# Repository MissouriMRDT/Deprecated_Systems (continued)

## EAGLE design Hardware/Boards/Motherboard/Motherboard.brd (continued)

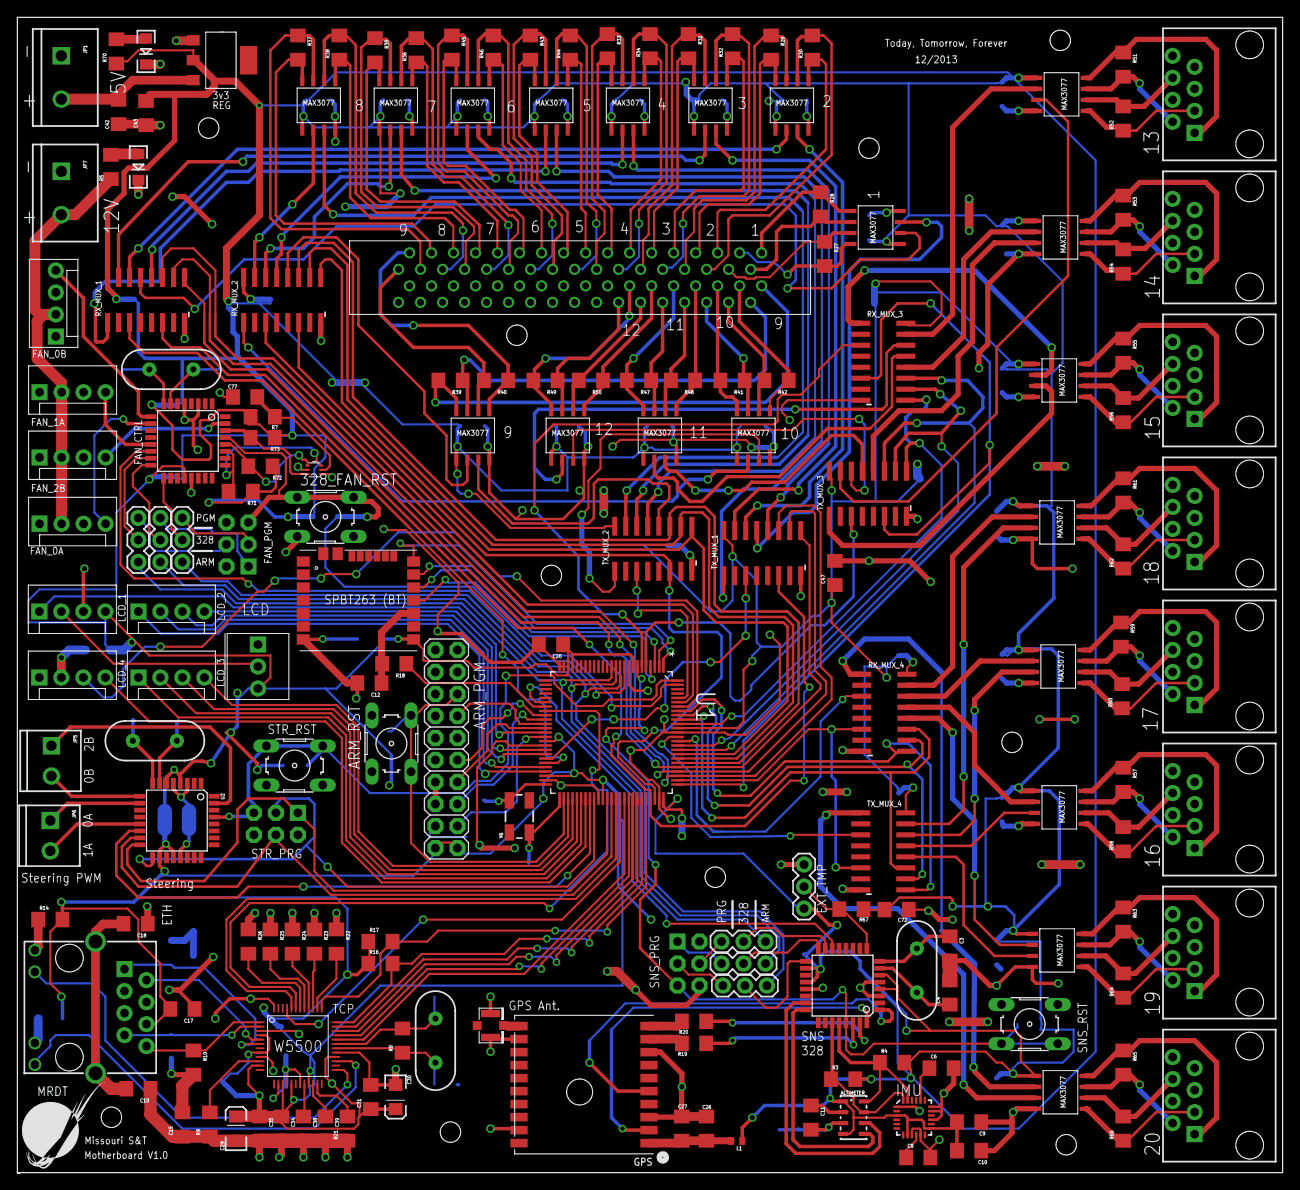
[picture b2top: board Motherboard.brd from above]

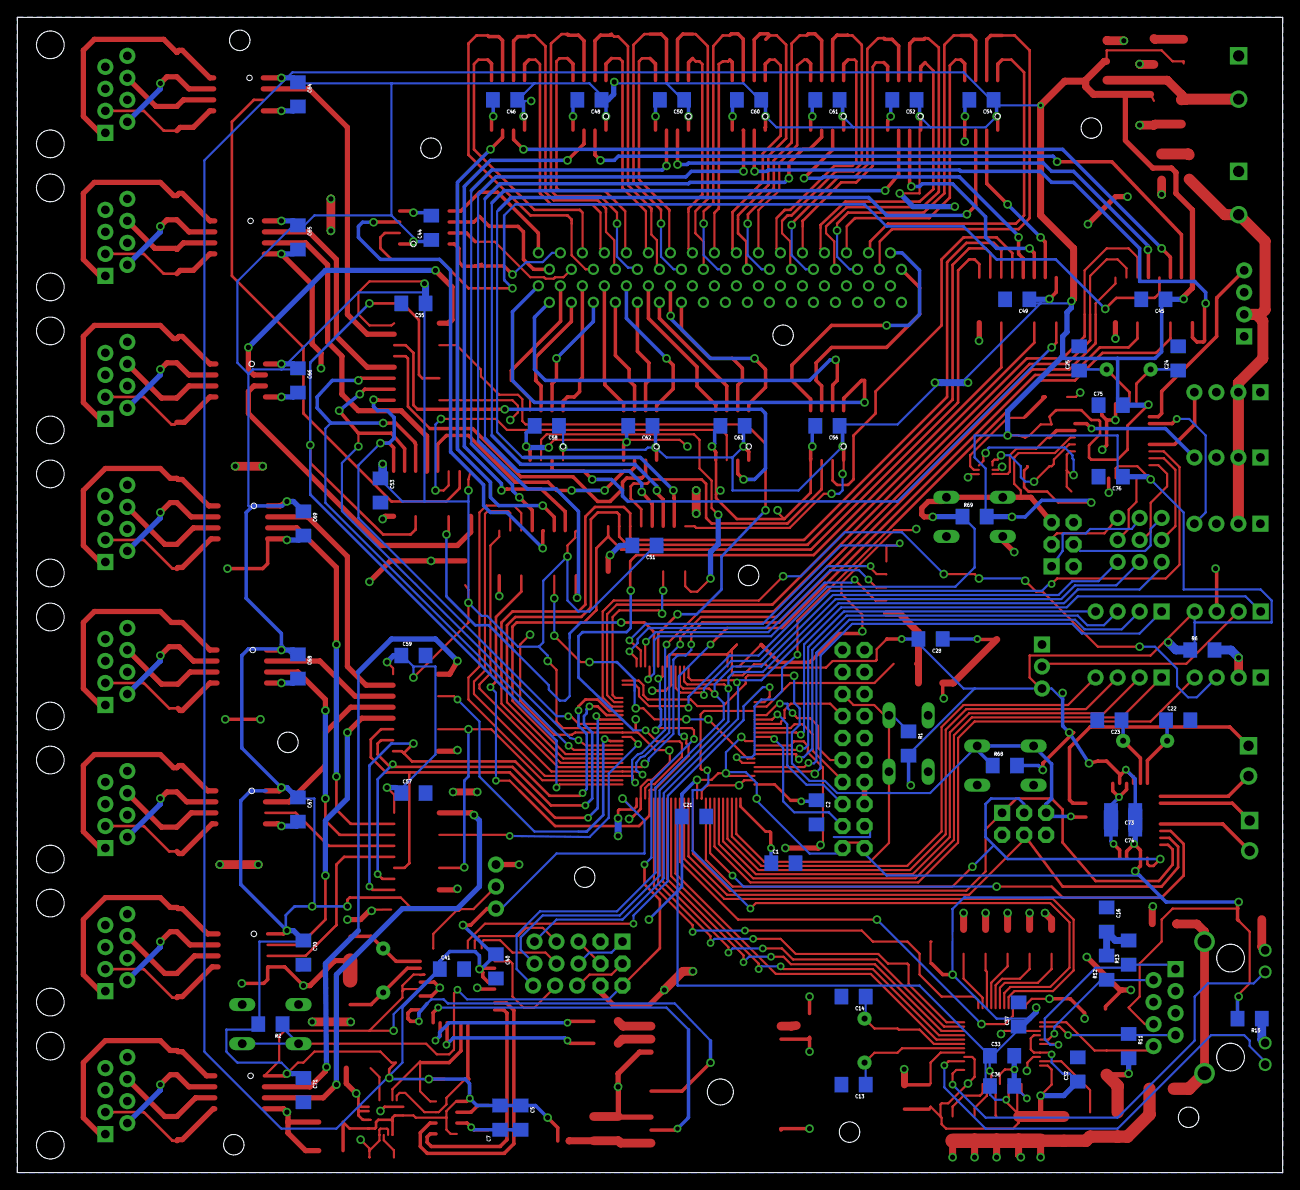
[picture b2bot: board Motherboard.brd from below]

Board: 2 copper layers, 146.1 x 133.3 mm, 236 parts (59 on the bottom side), 266 nets.

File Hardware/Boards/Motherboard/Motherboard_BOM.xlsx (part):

Part | Value | Device | Package |  | Part | Part Number | Quant | Supplier
 |  |  |  |  | Capacitors
328_FAN_RST | 10-XX | B3F-10XX | switch-omron |  | 22pF | 96K4783 | 6 | http://www.newark.com/avx/12061a220jat2a/capacitor-ceramic-2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
328_RST | 10-XX | B3F-10XX | switch-omron |  | .1uF | 96M1466 | 57 | http://www.newark.com/yageo/cc1206krx7r9bb104/capacitor-cera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
328_STR_RST | 10-XX | B3F-10XX | switch-omron |  | 2200pF | 30H0930 | 1 | http://www.newark.com/avx/12061a222jat2a/capacitor-ceramic-2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
ALTIMETER | MPL3115A2LGA8 | MPL3115A2LGA8 | LGA8 |  | 10nF/0.01uF | 96M1464 | 3 | http://www.newark.com/avx/12061c103jat2a/capacitor-ceramic-0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
ARM_RST | 10-XX | B3F-10XX | switch-omron |  | 18pF | 94W2957 | 2 | http://www.newark.com/avx/12065a180jat2a/capacitor-ceramic-1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
BLUETOOTH | SPBT2632C2A | SPBT2632C2A | SPBT2632C2A |  | 20pF | 70K9303 | 2 | http://www.newark.com/kemet/c1206c200j5gactu/capacitor-ceram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
C1 | 20pF | 1206 | SparkFun-Passives |  | 10uF | 60R6374 | 2 | http://www.newark.com/avx/12063d106kat2a/capacitor-ceramic-1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
C2 | 20pF | 1206 | SparkFun-Passives |  | 1uF | 96K4787 | 1 | http://www.newark.com/avx/12063c105kat2a/capacitor-ceramic-1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
C3 | 22pF | CAP1206 | 1206 |  | 4.7uF | 60R6372 | 1 | http://www.newark.com/avx/12061c103jat2a/capacitor-ceramic-0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
C4 | 22pF | CAP1206 | 1206 |  | 10uF (polarized) | 08X2301 | 2 | http://www.newark.com/vishay/293d106x9010a2te3/cap-tantalum-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
C5 | 100nF | CAP1206 | 1206
C6 | 2.2nF | CAP1206 | 1206
C7 | 10uF | CAP1206 | 1206 |  | Resistors
C8 | 0.1uF | CAP1206 | 1206 |  | 120 | 53K1957 | 40 | http://www.newark.com/vishay-dale/crcw1206120rfkea/resistor-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
C9 | 10nF | CAP1206 | 1206 |  | 10k | 61J5475 | 15 | http://www.newark.com/bourns/cr1206-fx-1002elf/resistor-thic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
C10 | 0.1uF | CAP1206 | 1206 |  | 330 | 32K3874 | 3 | http://www.newark.com/bourns/cr1206-fx-3300elf/resistor-thic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
C11 | 100nF | CAP1206 | 1206 |  | 1k | 32K3576 | 8 | http://www.newark.com/bourns/cr1206-fx-1001elf/resistor-thic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
C12 | 0.1uF | CAP1206 | 1206 |  | 51 | 53K2478 | 4 | http://www.newark.com/vishay-dale/crcw120651r0fkea/resistor-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
C13 | 18pF | CAP1206 | 1206 |  | 200 | 53K2137 | 2 | http://www.newark.com/vishay-dale/crcw1206200rfkea/resistor-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
C14 | 18pF | CAP1206 | 1206 |  | 1M | 32K3580 | 1 | http://www.newark.com/bourns/cr1206-fx-1004elf/resistor-thic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
C15 | .1uF | CAP1206 | 1206 |  | 12.4k | 53K1950 | 1 | http://www.newark.com/vishay-dale/crcw120612k4fkea/resistor-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
C16 | .1uF | CAP1206 | 1206
C17 | .1uF | CAP1206 | 1206
C18 | .1uF | CAP1206 | 1206 |  | Chips
C19 | .1uF | CAP1206 | 1206 |  | RS-485 transceiver | 700-MAX3077EESA | 20 | http://www.mouser.com/ProductDetail/Maxim-Integrated/MAX3077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
C20 | 0.1uF | CAP1206 | 1206 |  | Mux/Demux | 863-MC74LVXT8051DG | 8 | http://www.mouser.com/ProductDetail/ON-Semiconductor/MC74LVX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
C21 | 0.1uF | CAP1206 | 1206 |  | Bluetooth | 511-SPBT2632C2A.AT2 | 1 | http://www.mouser.com/ProductDetail/STMicroelectronics/SPBT2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
C22 | 22pF | CAP1206 | 1206 |  | altimeter | 841-MPL3115A2 | 1 | http://www.mouser.com/ProductDetail/Freescale-Semiconductor/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
C23 | 22pF | CAP1206 | 1206 |  | GPS | MTK3339 | 1 | http://www.adafruit.com/products/790#Description
C24 | 22pF | CAP1206 | 1206 |  | IMU | MPU-9150 | 1 | http://www.cdiweb.com/ProductDetail/MPU9150-InvenSense-Inc/7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
C25 | 22pF | CAP1206 | 1206 |  | ATMEGA328 | 556-ATMEGA328-AU | 3 | http://www.mouser.com/ProductDetail/Atmel/ATMEGA328-AU/?qs=s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
C26 | 1uF | CAP1206 | 1206 |  | TCP/IP | 950-W5500 | 1 | http://www.mouser.com/ProductDetail/WIZnet/W5500/?qs=sGAEpiM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
C27 | 0.01uF | CAP1206 | 1206 |  | on board temp | 86W6296 | 1 | http://www.newark.com/texas-instruments/tmp102aidrlr/sensor-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
C28 | 0.1uF | CAP1206 | 1206 |  | K10 Arm Chip | MK10DN512ZVLL10 | 1 | http://www.newark.com/freescale-semiconductor/mk10dn512zvll1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
C29 | 10uF/16V | CAP_POL1206 | EIA3216
C30 | 10uF/16V | CAP_POL1206 | EIA3216
C31 | 0.1uF | CAP1206 | 1206 |  | Misc.
C32 | 0.1uF | CAP1206 | 1206 |  | Ferrite Bead (L1) | 78R5663 | 1 | http://www.newark.com/wurth-elektronik/742792701/ferrite-bea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
C33 | 0.1uF | CAP1206 | 1206 |  | RJ45 (non-Magjack) | PRT-00643 | 8 | https://www.sparkfun.com/products/643
C34 | 0.1uF | CAP1206 | 1206 |  | RJ45 (Magjack) | PRT-08534 | 1 | https://www.sparkfun.com/products/8534
C35 | 0.1uF | CAP1206 | 1206 |  | 8Mhz crystal | 559-FOXS080-20-LF | 3 | http://www.mouser.com/ProductDetail/Fox/FOXSLF-080-20/?qs=sG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
C36 | 0.1uF | CAP1206 | 1206 |  | 25Mhz crystal | 559-FOXS250F-20-LF | 1 | http://www.mouser.com/ProductDetail/Fox/FOXSLF-250F-20/?qs=s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
C37 | 0.1uF | CAP1206 | 1206 |  | 3.3V Voltage Reg | 89K0626 | 1 | http://www.newark.com/stmicroelectronics/ld1117s33ctr/ic-ldo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
C38 | 4.7uF | CAP1206 | 1206 |  | u.Fl connector | 960-RECE20279001E01 | 1 | http://www.mouser.com/ProductDetail/Taoglas/RECE-20279-001E-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
C39 | 10nF | CAP1206 | 1206 |  | outside temp | AM2302 | 1 | http://www.adafruit.com/products/393#Downloads
C40 | 0.1uF | CAP1206 | 1206 |  | molex 1X4 | TOL-11300 | 6 | https://www.sparkfun.com/products/11300
C41 | 0.1uF | CAP1206 | 1206 |  | Reset Switches | B3F-10XX | 4 | http://www.adafruit.com/products/367
C42 | 100nF | CAP1206 | 1206 |  | 2 Pin 5 MM Screw T. |  | 4 | https://www.sparkfun.com/products/8432
C43 | 10uF | CAP1206 | 1206 |  | 3 Pin 5 MM Screw T. |  | 1 | https://www.sparkfun.com/products/8433
C44 | 0.1uF | CAP1206 | 1206 |  | LCD Screen | LCD-09051 | 1 | https://www.sparkfun.com/products/9051
C45 | 0.1uF | CAP1206 | 1206 |  | 32MHz Crystal
C46 | 0.1uF | CAP1206 | 1206 |  | Ribbon Cable connector
C47 | 0.1uF | CAP1206 | 1206 |  | Arm Programming headers
C48 | 0.1uF | CAP1206 | 1206 |  | AVR Programming headers
C49 | 0.1uF | CAP1206 | 1206 |  | Green SMD Leds
C50 | 0.1uF | CAP1206 | 1206
C51 | 0.1uF | CAP1206 | 1206 |  | Parts Not Listed
C52 | 0.1uF | CAP1206 | 1206
C53 | 0.1uF | CAP1206 | 1206 |  | TTL Converter
C54 | 0.1uF | CAP1206 | 1206
C55 | 0.1uF | CAP1206 | 1206
C56 | 0.1uF | CAP1206 | 1206
C57 | 0.1uF | CAP1206 | 1206
C58 | 0.1uF | CAP1206 | 1206
C59 | 0.1uF | CAP1206 | 1206
C60 | 0.1uF | CAP1206 | 1206
C61 | 0.1uF | CAP1206 | 1206
C62 | 0.1uF | CAP1206 | 1206
C63 | 0.1uF | CAP1206 | 1206
C64 | 0.1uF | CAP1206 | 1206
C65 | 0.1uF | CAP1206 | 1206
C66 | 0.1uF | CAP1206 | 1206
C67 | 0.1uF | CAP1206 | 1206
C68 | 0.1uF | CAP1206 | 1206
C69 | 0.1uF | CAP1206 | 1206
C70 | 0.1uF | CAP1206 | 1206
C71 | 0.1uF | CAP1206 | 1206
C72 | 100nF | CAP1206 | 1206
C73 | 0.1uF | CAP1206 | 1206
C74 | 0.1uF | CAP1206 | 1206
C75 | 0.1uF | CAP1206 | 1206
C76 | 0.1uF | CAP1206 | 1206
D1 | GREEN | LED-GREENLARGE | LED-1206
GPS | GPS_FGPMMOPA6H | FGPMMOPA6H | adafruit
IMU | MPU-9150QFN-24-NP | QFN-24-NP | SparkFun-Sensors
J1 | AVR_SPI_PRG_6NS | AVR_SPI_PRG_6NS | 2X3-NS
J2 | U.FL | U.FL | U.FL
J3 | MAGJACK | MAGJACK | MAGJACK
JP1 | M025MM | M025MM | SCREWTERMINAL-5MM-2
JP2 | M03-SCREW-5MM | SCREWTERMINAL-5MM-3 | SparkFun-Connectors
JP3 | M04POLAR | MOLEX-1X4 | SparkFun-Connectors
JP4 | M04POLAR | MOLEX-1X4 | SparkFun-Connectors
JP5 | M03-SCREW-5MM | SCREWTERMINAL-5MM-3 | SparkFun-Connectors
JP6 | M03-SCREW-5MM | SCREWTERMINAL-5MM-3 | SparkFun-Connectors
JP7 | M025MM | M025MM | SCREWTERMINAL-5MM-2
JP8 | M04POLAR | MOLEX-1X4 | SparkFun-Connectors
JP9 | M04POLAR | MOLEX-1X4 | SparkFun-Connectors
JP10 | M04POLAR | MOLEX-1X4 | SparkFun-Connectors
JP11 | M04POLAR | MOLEX-1X4 | SparkFun-Connectors
JTAG_CON | M10X2 | M10X2 | 2X10 |  | Arm Programming headers
L1 | BML15HB121SN1 | BML15HB121SN1 | 402
R1 | 10k | 1206 | SparkFun-Resistors
R2 | 10k | RESISTOR1206 | 1206
R3 | 10k | RESISTOR1206 | 1206
R4 | 10k | RESISTOR1206 | 1206
R5 | 1k | RESISTOR1206 | 1206
R6 | 1k | RESISTOR1206 | 1206
R7 | 1k | RESISTOR1206 | 1206
R8 | 1M | RESISTOR1206 | 1206
R9 | 12.4K | RESISTOR1206 | 1206
R10 | 51 | RESISTOR1206 | 1206
R11 | 51 | RESISTOR1206 | 1206
R12 | 51 | RESISTOR1206 | 1206
R13 | 51 | RESISTOR1206 | 1206
R14 | 200 | RESISTOR1206 | 1206
R15 | 200 | RESISTOR1206 | 1206
R16 | 10K | RESISTOR1206 | 1206
R17 | 10K | RESISTOR1206 | 1206
R18 | 10k | RESISTOR1206 | 1206
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
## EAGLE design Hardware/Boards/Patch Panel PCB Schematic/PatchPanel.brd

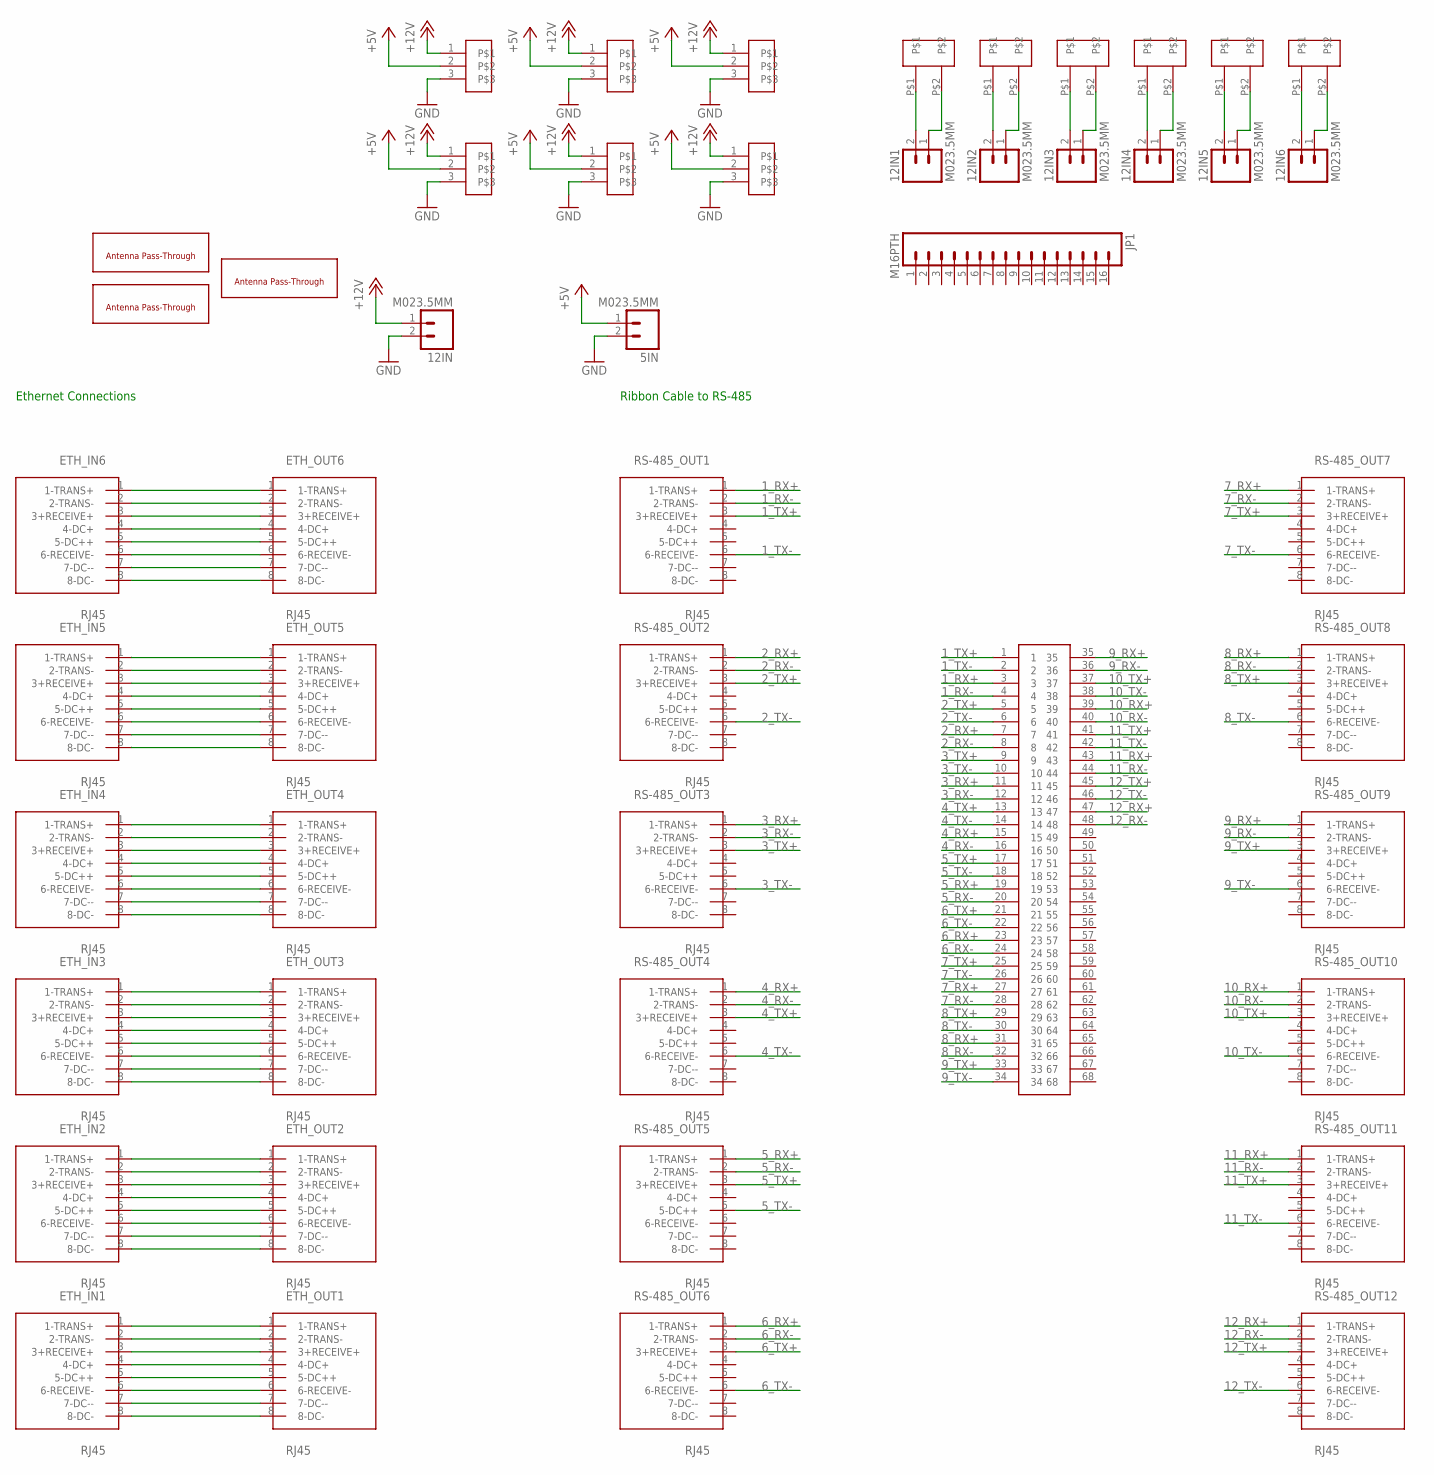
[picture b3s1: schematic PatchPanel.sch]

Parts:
5IN, 12IN, 12IN1, 12IN2, 12IN3, 12IN4, 12IN5, 12IN6: M023.5MM; SCREWTERMINAL-3.5MM-2
ETH_IN1, ETH_IN2, ETH_IN3, ETH_IN4, ETH_IN5, ETH_IN6: RJ45; RJ45-CAT5E
ETH_OUT1, ETH_OUT2, ETH_OUT3, ETH_OUT4, ETH_OUT5, ETH_OUT6: RJ45; RJ45-CAT5E
JP1: M16PTH; 1X16
RS-485_OUT1, RS-485_OUT2, RS-485_OUT3, RS-485_OUT4, RS-485_OUT5, RS-485_OUT6, RS-485_OUT7, RS-485_OUT8, RS-485_OUT9, RS-485_OUT10, RS-485_OUT11, RS-485_OUT12: RJ45; RJ45-CAT5E
U$1: TB60050685100; 60050685100
U$2, U$3, U$4, U$5, U$6, U$7: 3PIN; 0.93"
U$8, U$9, U$10, U$11, U$12, U$13: MLX-2; 42002-2
U$14, U$15: N-TYPE-THRU; N-TYPE
U$16: SMA-THRU; SMA

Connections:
1_RX+: RS-485_OUT1.1 (1-TRANS+), U$1.3
1_RX-: RS-485_OUT1.2 (2-TRANS-), U$1.4
1_TX+: RS-485_OUT1.3 (3+RECEIVE+), U$1.1
1_TX-: RS-485_OUT1.6 (6-RECEIVE-), U$1.2
2_RX+: RS-485_OUT2.1 (1-TRANS+), U$1.7
2_RX-: RS-485_OUT2.2 (2-TRANS-), U$1.8
2_TX+: RS-485_OUT2.3 (3+RECEIVE+), U$1.5
2_TX-: RS-485_OUT2.6 (6-RECEIVE-), U$1.6
3_RX+: RS-485_OUT3.1 (1-TRANS+), U$1.11
3_RX-: RS-485_OUT3.2 (2-TRANS-), U$1.12
3_TX+: RS-485_OUT3.3 (3+RECEIVE+), U$1.9
3_TX-: RS-485_OUT3.6 (6-RECEIVE-), U$1.10
4_RX+: RS-485_OUT4.1 (1-TRANS+), U$1.15
4_RX-: RS-485_OUT4.2 (2-TRANS-), U$1.16
4_TX+: RS-485_OUT4.3 (3+RECEIVE+), U$1.13
4_TX-: RS-485_OUT4.6 (6-RECEIVE-), U$1.14
5_RX+: RS-485_OUT5.1 (1-TRANS+), U$1.19
5_RX-: RS-485_OUT5.2 (2-TRANS-), U$1.20
5_TX+: RS-485_OUT5.3 (3+RECEIVE+), U$1.17
5_TX-: RS-485_OUT5.5 (5-DC++), U$1.18
6_RX+: RS-485_OUT6.1 (1-TRANS+), U$1.23
6_RX-: RS-485_OUT6.2 (2-TRANS-), U$1.24
6_TX+: RS-485_OUT6.3 (3+RECEIVE+), U$1.21
6_TX-: RS-485_OUT6.6 (6-RECEIVE-), U$1.22
7_RX+: RS-485_OUT7.1 (1-TRANS+), U$1.27
7_RX-: RS-485_OUT7.2 (2-TRANS-), U$1.28
7_TX+: RS-485_OUT7.3 (3+RECEIVE+), U$1.25
7_TX-: RS-485_OUT7.6 (6-RECEIVE-), U$1.26
8_RX+: RS-485_OUT8.1 (1-TRANS+), U$1.31
8_RX-: RS-485_OUT8.2 (2-TRANS-), U$1.32
8_TX+: RS-485_OUT8.3 (3+RECEIVE+), U$1.29
8_TX-: RS-485_OUT8.6 (6-RECEIVE-), U$1.30
9_RX+: RS-485_OUT9.1 (1-TRANS+), U$1.35
9_RX-: RS-485_OUT9.2 (2-TRANS-), U$1.36
9_TX+: RS-485_OUT9.3 (3+RECEIVE+), U$1.33
9_TX-: RS-485_OUT9.6 (6-RECEIVE-), U$1.34
10_RX+: RS-485_OUT10.1 (1-TRANS+), U$1.39
10_RX-: RS-485_OUT10.2 (2-TRANS-), U$1.40
10_TX+: RS-485_OUT10.3 (3+RECEIVE+), U$1.37
10_TX-: RS-485_OUT10.6 (6-RECEIVE-), U$1.38
11_RX+: RS-485_OUT11.1 (1-TRANS+), U$1.43
11_RX-: RS-485_OUT11.2 (2-TRANS-), U$1.44
11_TX+: RS-485_OUT11.3 (3+RECEIVE+), U$1.41
11_TX-: RS-485_OUT11.6 (6-RECEIVE-), U$1.42
12_RX+: RS-485_OUT12.1 (1-TRANS+), U$1.47
12_RX-: RS-485_OUT12.2 (2-TRANS-), U$1.48
12_TX+: RS-485_OUT12.3 (3+RECEIVE+), U$1.45
12_TX-: RS-485_OUT12.6 (6-RECEIVE-), U$1.46
+5V: 5IN.1, U$2.2, U$3.2, U$4.2, U$5.2, U$6.2, U$7.2
+12V: 12IN.1, U$2.1, U$3.1, U$4.1, U$5.1, U$6.1, U$7.1
GND: 5IN.2, 12IN.2, U$2.3, U$3.3, U$4.3, U$5.3, U$6.3, U$7.3
unnamed: ETH_IN1.1 (1-TRANS+), ETH_OUT1.1 (1-TRANS+)
unnamed: ETH_IN1.2 (2-TRANS-), ETH_OUT1.2 (2-TRANS-)
unnamed: ETH_IN1.3 (3+RECEIVE+), ETH_OUT1.3 (3+RECEIVE+)
unnamed: ETH_IN1.4 (4-DC+), ETH_OUT1.4 (4-DC+)
unnamed: ETH_IN1.5 (5-DC++), ETH_OUT1.5 (5-DC++)
unnamed: ETH_IN1.6 (6-RECEIVE-), ETH_OUT1.6 (6-RECEIVE-)
unnamed: ETH_IN1.7 (7-DC--), ETH_OUT1.7 (7-DC--)
unnamed: ETH_IN1.8 (8-DC-), ETH_OUT1.8 (8-DC-)
unnamed: ETH_IN2.1 (1-TRANS+), ETH_OUT2.1 (1-TRANS+)
unnamed: ETH_IN2.2 (2-TRANS-), ETH_OUT2.2 (2-TRANS-)
unnamed: ETH_IN2.3 (3+RECEIVE+), ETH_OUT2.3 (3+RECEIVE+)
unnamed: ETH_IN2.4 (4-DC+), ETH_OUT2.4 (4-DC+)
unnamed: ETH_IN2.5 (5-DC++), ETH_OUT2.5 (5-DC++)
unnamed: ETH_IN2.6 (6-RECEIVE-), ETH_OUT2.6 (6-RECEIVE-)
unnamed: ETH_IN2.7 (7-DC--), ETH_OUT2.7 (7-DC--)
unnamed: ETH_IN2.8 (8-DC-), ETH_OUT2.8 (8-DC-)
unnamed: ETH_IN3.1 (1-TRANS+), ETH_OUT3.1 (1-TRANS+)
unnamed: ETH_IN3.2 (2-TRANS-), ETH_OUT3.2 (2-TRANS-)
unnamed: ETH_IN3.3 (3+RECEIVE+), ETH_OUT3.3 (3+RECEIVE+)
unnamed: ETH_IN3.4 (4-DC+), ETH_OUT3.4 (4-DC+)
unnamed: ETH_IN3.5 (5-DC++), ETH_OUT3.5 (5-DC++)
unnamed: ETH_IN3.6 (6-RECEIVE-), ETH_OUT3.6 (6-RECEIVE-)
unnamed: ETH_IN3.7 (7-DC--), ETH_OUT3.7 (7-DC--)
unnamed: ETH_IN3.8 (8-DC-), ETH_OUT3.8 (8-DC-)
unnamed: ETH_IN4.8 (8-DC-), ETH_OUT4.8 (8-DC-)
unnamed: ETH_IN4.7 (7-DC--), ETH_OUT4.7 (7-DC--)
unnamed: ETH_IN4.6 (6-RECEIVE-), ETH_OUT4.6 (6-RECEIVE-)
unnamed: ETH_IN4.5 (5-DC++), ETH_OUT4.5 (5-DC++)
unnamed: ETH_IN4.4 (4-DC+), ETH_OUT4.4 (4-DC+)
unnamed: ETH_IN4.3 (3+RECEIVE+), ETH_OUT4.3 (3+RECEIVE+)
unnamed: ETH_IN4.2 (2-TRANS-), ETH_OUT4.2 (2-TRANS-)
unnamed: ETH_IN4.1 (1-TRANS+), ETH_OUT4.1 (1-TRANS+)
unnamed: ETH_IN5.8 (8-DC-), ETH_OUT5.8 (8-DC-)
unnamed: ETH_IN5.7 (7-DC--), ETH_OUT5.7 (7-DC--)
unnamed: ETH_IN5.6 (6-RECEIVE-), ETH_OUT5.6 (6-RECEIVE-)
unnamed: ETH_IN5.5 (5-DC++), ETH_OUT5.5 (5-DC++)
unnamed: ETH_IN5.4 (4-DC+), ETH_OUT5.4 (4-DC+)
unnamed: ETH_IN5.3 (3+RECEIVE+), ETH_OUT5.3 (3+RECEIVE+)
unnamed: ETH_IN5.2 (2-TRANS-), ETH_OUT5.2 (2-TRANS-)
unnamed: ETH_IN5.1 (1-TRANS+), ETH_OUT5.1 (1-TRANS+)
unnamed: ETH_IN6.1 (1-TRANS+), ETH_OUT6.1 (1-TRANS+)
unnamed: ETH_IN6.2 (2-TRANS-), ETH_OUT6.2 (2-TRANS-)
unnamed: ETH_IN6.3 (3+RECEIVE+), ETH_OUT6.3 (3+RECEIVE+)
unnamed: ETH_IN6.4 (4-DC+), ETH_OUT6.4 (4-DC+)
unnamed: ETH_IN6.5 (5-DC++), ETH_OUT6.5 (5-DC++)
unnamed: ETH_IN6.6 (6-RECEIVE-), ETH_OUT6.6 (6-RECEIVE-)
unnamed: ETH_IN6.7 (7-DC--), ETH_OUT6.7 (7-DC--)
unnamed: ETH_IN6.8 (8-DC-), ETH_OUT6.8 (8-DC-)
unnamed: 12IN1.2, U$8.P$1
unnamed: 12IN1.1, U$8.P$2
unnamed: 12IN2.2, U$9.P$1
unnamed: 12IN2.1, U$9.P$2
unnamed: 12IN3.2, U$10.P$1
unnamed: 12IN3.1, U$10.P$2
unnamed: 12IN4.2, U$11.P$1
unnamed: 12IN4.1, U$11.P$2
unnamed: 12IN5.2, U$12.P$1
unnamed: 12IN5.1, U$12.P$2
unnamed: 12IN6.2, U$13.P$1
unnamed: 12IN6.1, U$13.P$2

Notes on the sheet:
Ethernet Connections
Ribbon Cable to RS-485

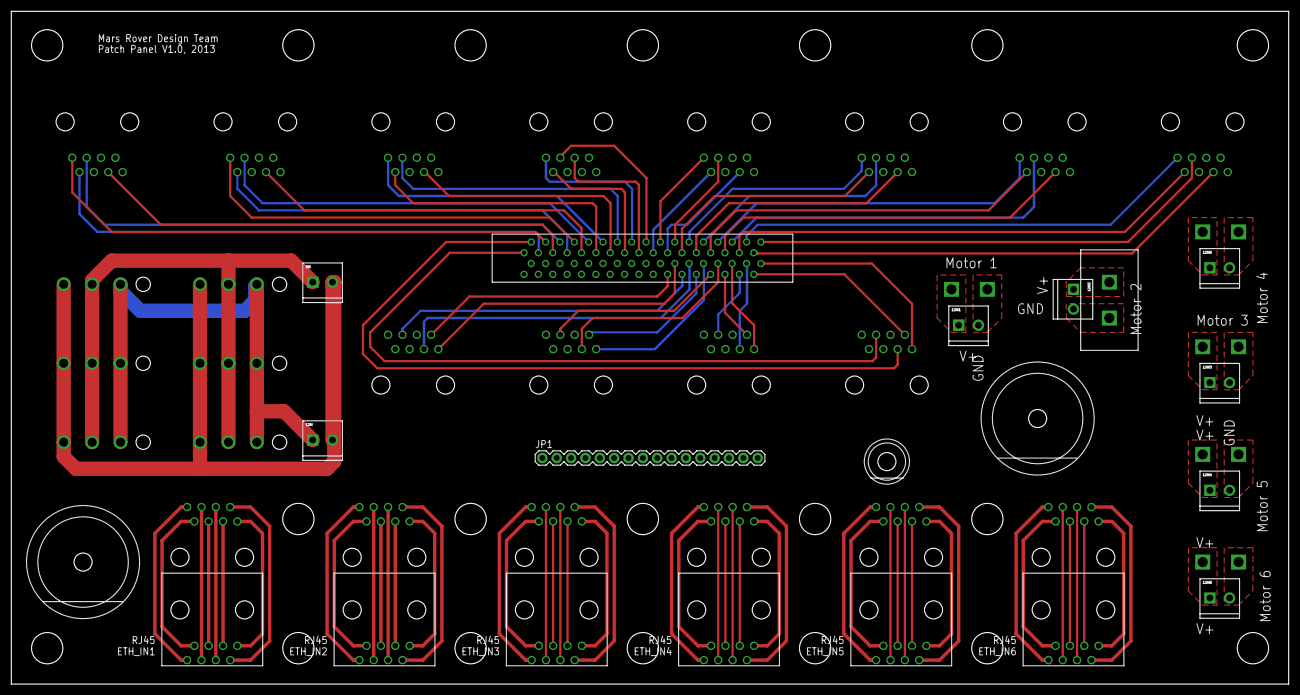
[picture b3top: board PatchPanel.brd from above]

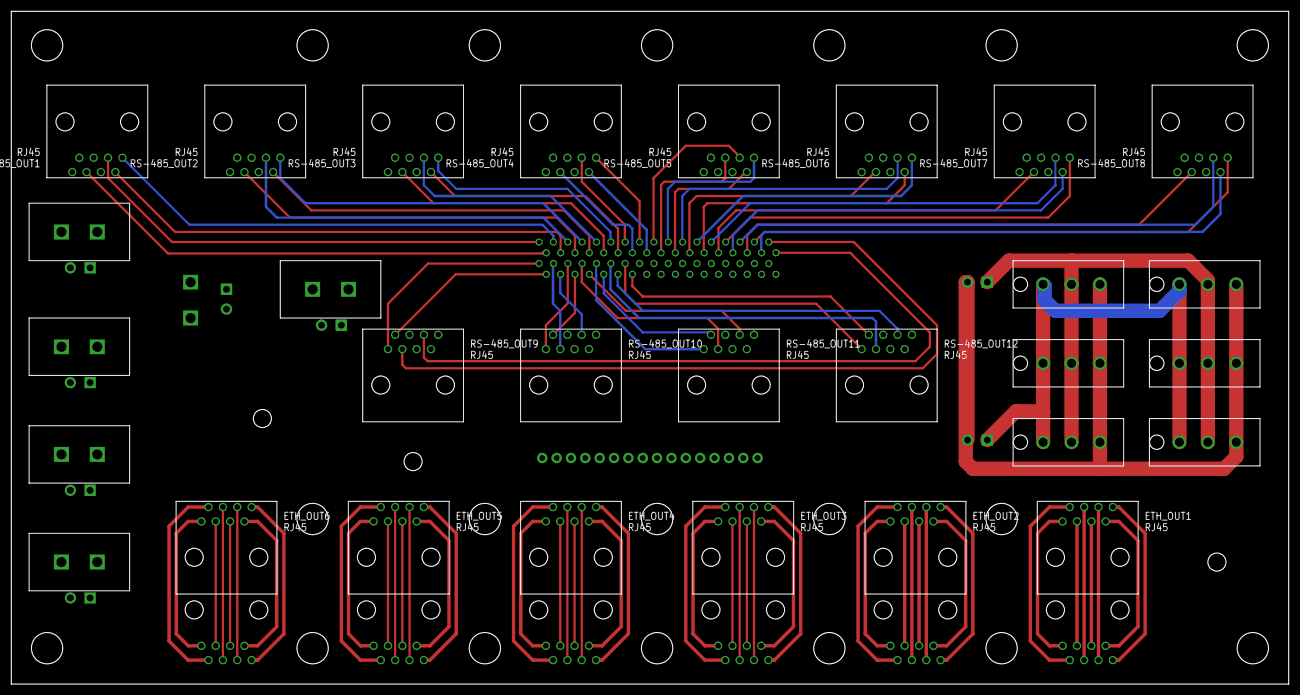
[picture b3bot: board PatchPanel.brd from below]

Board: 2 copper layers, 226.0 x 119.0 mm, 49 parts (29 on the bottom side), 111 nets.

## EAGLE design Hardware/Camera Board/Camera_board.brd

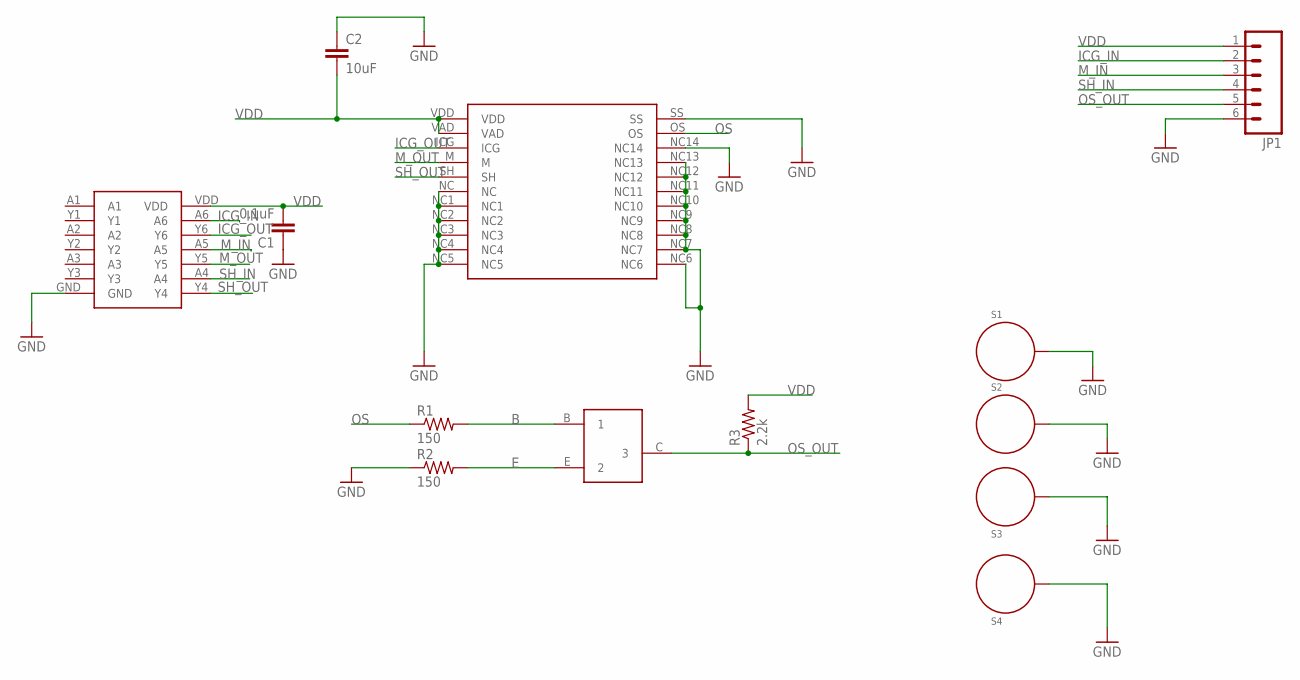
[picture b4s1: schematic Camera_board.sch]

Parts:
C1: 0.1uF; 1206
C2: 10uF; 1206
JP1: M06POLAR; MOLEX-1X6
R1, R2: 150; 1206
R3: 2.2k; 1206
S1, S2, S3, S4: STANDOFF_ELECTRICAL; STANDOFF-ELECTRICAL
U$1: TRANSISTOR; SOT23-BEC
U$2: CCDCAMERA
U$3: CMOS_HEX_INVERTER

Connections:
B: R1.2, U$1.B (1)
E: R2.2, U$1.E (2)
GND: C1.1, C2.1, JP1.6, R2.1, S1.P1, S2.P1, S3.P1, S4.P1, U$2.NC, U$2.NC1, U$2.NC2, U$2.NC3, U$2.NC4, U$2.NC5, U$2.NC6, U$2.NC7, U$2.NC8, U$2.NC9, U$2.NC10, U$2.NC11, U$2.NC12, U$2.NC13, U$2.NC14, U$2.SS, U$3.GND
ICG_IN: JP1.2, U$3.A6
ICG_OUT: U$2.ICG, U$3.Y6
M_IN: JP1.3, U$3.A5
M_OUT: U$2.M, U$3.Y5
OS: R1.1, U$2.OS
OS_OUT: JP1.5, R3.1, U$1.C (3)
SH_IN: JP1.4, U$3.A4
SH_OUT: U$2.SH, U$3.Y4
VDD: C1.2, C2.2, JP1.1, R3.2, U$2.VAD, U$2.VDD, U$3.VDD

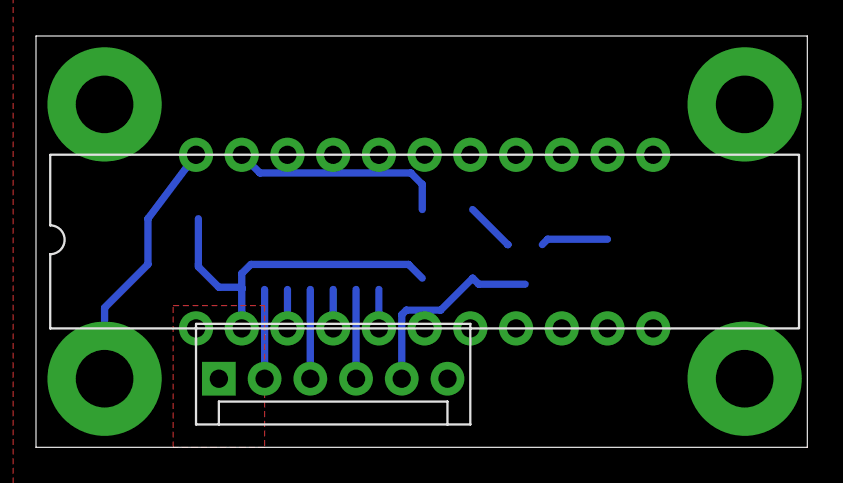
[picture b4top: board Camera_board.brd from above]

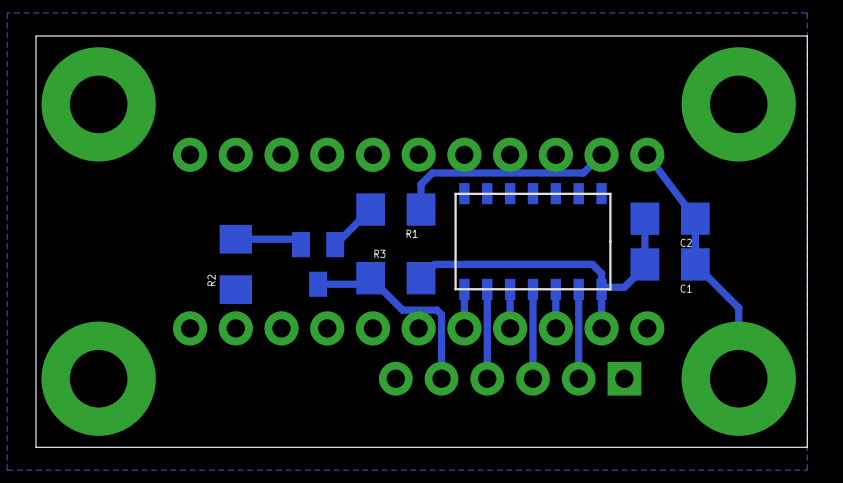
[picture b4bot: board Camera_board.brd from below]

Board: 2 copper layers, 42.9 x 22.9 mm, 13 parts (7 on the bottom side), 12 nets.

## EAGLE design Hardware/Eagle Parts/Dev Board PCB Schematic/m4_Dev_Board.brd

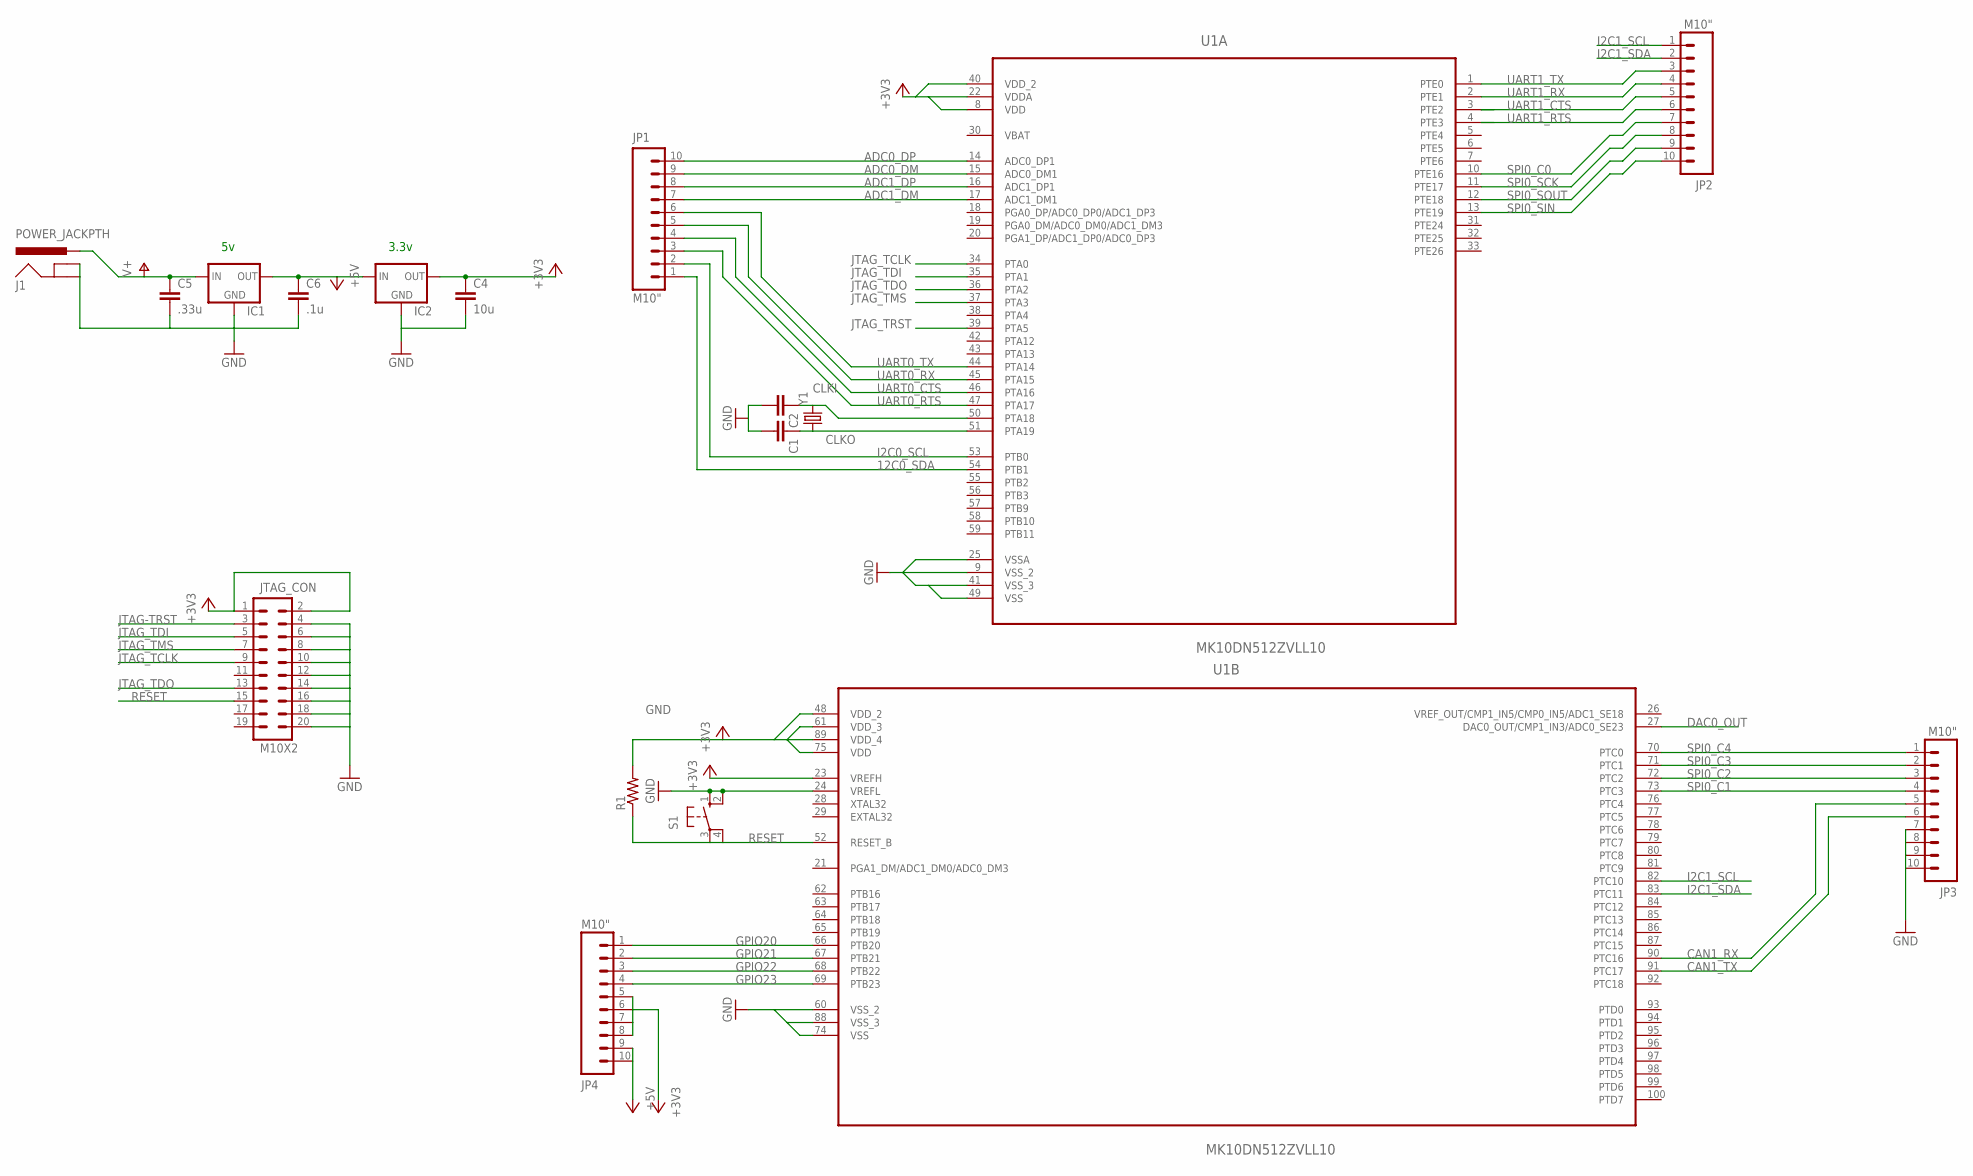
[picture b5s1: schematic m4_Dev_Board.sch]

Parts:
C1, C2: CAPPTH1; CAP-PTH-5MM
C4: 10u; CAP-PTH-5MM
C5: .33u; CAP-PTH-5MM
C6: .1u; CAP-PTH-5MM
IC1, IC2: V_REG_78XXSINK; TO220-IGO
J1: POWER_JACKPTH; POWER_JACK_PTH
JP1, JP2, JP3, JP4: M10"; 1X10
JTAG_CON: M10X2; 2X10
R1: RESISTORPTH-1/4W; AXIAL-0.4
S1: 10-XX; B3F-10XX
U1: MK10DN512ZVLL10; QFP50P1600X1600X170-100N
Y1: CRYSTALHC49US; HC49US

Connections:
12C0_SDA: JP1.1, U1.54 (PTB1)
+3V3: C4.1, IC2.OUT, JP4.5, JP4.6, JP4.7, JP4.8, JTAG_CON.1, JTAG_CON.2, R1.P$2 (2), U1.8 (VDD), U1.22 (VDDA), U1.23 (VREFH), U1.40 (VDD_2), U1.48 (VDD_2), U1.61 (VDD_3), U1.75 (VDD), U1.89 (VDD_4); also elsewhere on the board
+5V: C6.1, IC1.OUT, IC2.IN, JP4.9, JP4.10
ADC0_DM: JP1.9, U1.15 (ADC0_DM1)
ADC0_DP: JP1.10, U1.14 (ADC0_DP1)
ADC1_DM: JP1.7, U1.17 (ADC1_DM1)
ADC1_DP: JP1.8, U1.16 (ADC1_DP1)
CAN1_RX: JP3.5, U1.90 (PTC16)
CAN1_TX: JP3.6, U1.91 (PTC17)
CLKI: C2.1, U1.50 (PTA18), Y1.2
CLKO: C1.1, U1.51 (PTA19), Y1.1
DAC0_OUT: U1.27 (DAC0_OUT/CMP1_IN3/ADC0_SE23)
GND: C1.2, C2.2, C4.2, C5.2, C6.2, IC1.GND, IC2.GND, J1.GND, J1.GNDBREAK, JP3.7, JP3.8, JP3.9, JP3.10, JTAG_CON.4, JTAG_CON.6, JTAG_CON.8, JTAG_CON.10, JTAG_CON.12, JTAG_CON.14, JTAG_CON.16, JTAG_CON.18, JTAG_CON.20, S1.1 (S), S1.2 (S1), U1.9 (VSS_2), U1.24 (VREFL), U1.25 (VSSA), U1.41 (VSS_3), U1.49 (VSS), U1.60 (VSS_2), U1.74 (VSS), U1.88 (VSS_3)
GPIO20: JP4.1, U1.66 (PTB20)
GPIO21: JP4.2, U1.67 (PTB21)
GPIO22: JP4.3, U1.68 (PTB22)
GPIO23: JP4.4, U1.69 (PTB23)
I2C0_SCL: JP1.2, U1.53 (PTB0)
I2C1_SCL: JP2.1, U1.82 (PTC10); also elsewhere on the board
I2C1_SDA: JP2.2, U1.83 (PTC11); also elsewhere on the board
JTAG-TRST: JTAG_CON.3
JTAG_TCLK: JTAG_CON.9, U1.34 (PTA0)
JTAG_TDI: JTAG_CON.5, U1.35 (PTA1)
JTAG_TDO: JTAG_CON.13, U1.36 (PTA2)
JTAG_TMS: JTAG_CON.7, U1.37 (PTA3)
JTAG_TRST: U1.39 (PTA5)
RESET: JTAG_CON.15, R1.P$1 (1), S1.3, S1.4 (P1), U1.52 (RESET_B)
SPI0_C0: JP2.7, U1.10 (PTE16)
SPI0_C1: JP3.4, U1.73 (PTC3)
SPI0_C2: JP3.3, U1.72 (PTC2)
SPI0_C3: JP3.2, U1.71 (PTC1)
SPI0_C4: JP3.1, U1.70 (PTC0)
SPI0_SCK: JP2.8, U1.11 (PTE17)
SPI0_SIN: JP2.10, U1.13 (PTE19)
SPI0_SOUT: JP2.9, U1.12 (PTE18)
UART0_CTS: JP1.4, U1.46 (PTA16)
UART0_RTS: JP1.3, U1.47 (PTA17)
UART0_RX: JP1.5, U1.45 (PTA15)
UART0_TX: JP1.6, U1.44 (PTA14)
UART1_CTS: JP2.5, U1.3 (PTE2)
UART1_RTS: JP2.6, U1.4 (PTE3)
UART1_RX: JP2.4, U1.2 (PTE1)
UART1_TX: JP2.3, U1.1 (PTE0)
V+: C5.1, IC1.IN, J1.PWR
VBAT: U1.30 (VBAT)

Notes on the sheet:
3.3v

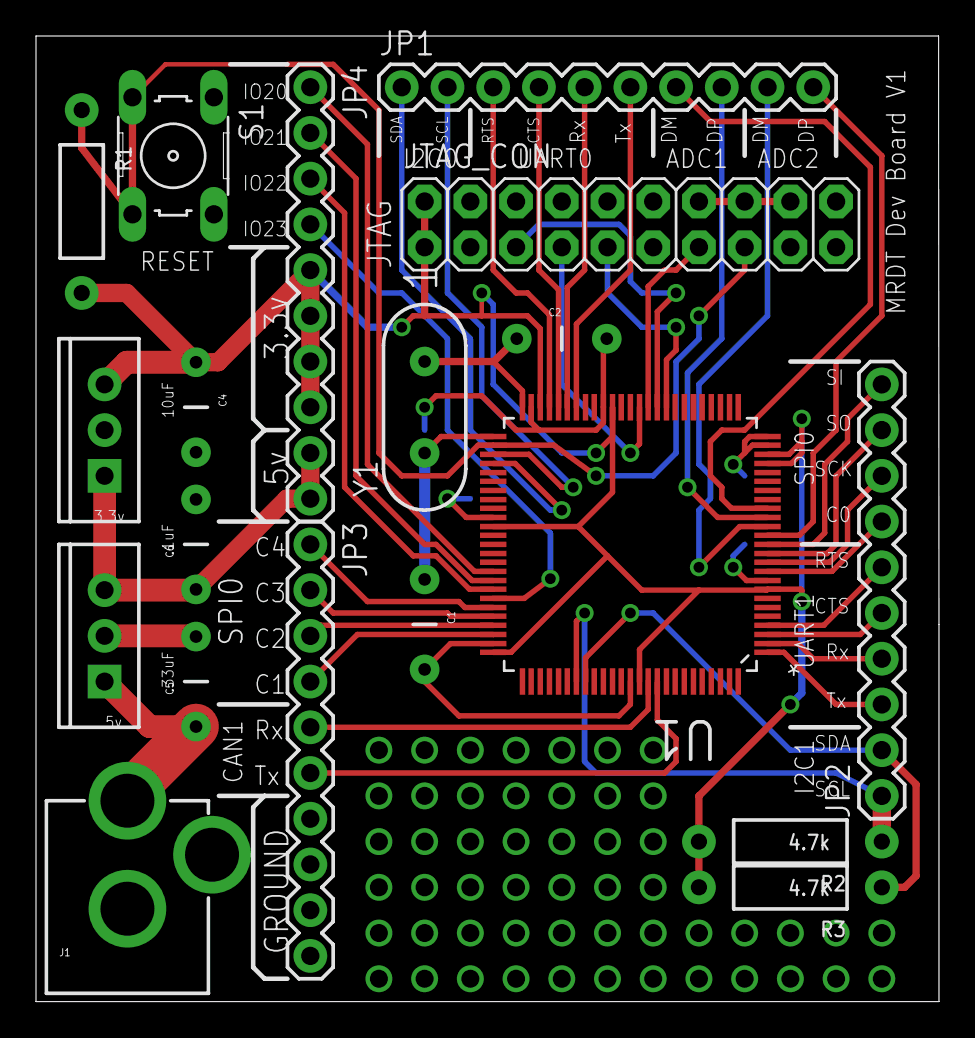
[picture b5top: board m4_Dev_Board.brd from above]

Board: 2 copper layers, 50.2 x 53.6 mm, 19 parts (0 on the bottom side), 41 nets.

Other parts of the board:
R2, R3: 4.7k; AXIAL-0.4

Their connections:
+3V3: R2.P$2, R3.P$2; also elsewhere on the board
I2C1_SCL: R2.P$1; also elsewhere on the board
I2C1_SDA: R3.P$1; also elsewhere on the board
